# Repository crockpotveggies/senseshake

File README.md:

# Groundlark — an open source seismic acquisition platform with support for FPGAs and BISCUT AI chips

Groundlark is an open hardware seismic acquisition platform combining a
Raspberry Pi, a three-IMU DAQHAT-01 sensor HAT, a Trenz Artix-7 200T FPGA module,
and a passive geophone.

The image uses current HAT CAD and the vendor Trenz model. The Pi, baseline
socket and geophone are conceptual geometry; lead routing is illustrative.
The J1 procurement substitute needs a physical stack-height check.

## Hardware

The [DAQHAT-01](docs/trenz-hat.md) is an 85 × 56 mm, six-layer FR-4 carrier with
three XYZ LSM6DSO IMUs and one ADS122C04 input for an external Racotech geophone.
The stack is **Pi → HAT → Trenz FPGA**. It requires a separate regulated
3.3 V-class FPGA supply; follow the guide's voltage and power limits.

The [internal FPGA link](docs/fpga-host-link.md) reserves six QSPI wires and
supports UART, reset and switched Pi-driven JTAG without external ribbon cables.
Pi 4 initially uses SPI6; native quad transfers require a different host solution.
An SPI echo bitstream is implemented; accelerated sensor processing remains future work.

The [USB-C sensor head](docs/usb-sensor-head.md) carries an RM3100 magnetometer
and optional DLVR infrasound sensor. It connects to the Pi for power and data;
its MCU firmware is still pending. These sensors are separate from the HAT.
The [A2 ASIC HAT](docs/design-a0.md) and [Coldfoot integration](docs/coldfoot-integration.md)
are retained as a separate design; current hardware work focuses on the FPGA stack.

Use the [stack assembly guide](docs/stack-assembly.md) and
[JLCPCB instructions](docs/jlcpcb-assembly.md) for mechanical and manufacturing details.
The JLCPCB package targets **one assembled HAT**. Upload the corrected BOM and
CPL together. Supplier quantity, sourcing, placement and J1 fit checks remain open.
Fabrication packages stay local under ignored `hw/releases/`.

Physical power, fit, timing, noise and thermal qualification remain pending.
The [bench procedure](docs/bench-procedure.md) describes the required measurements.

## Sensor workbench

The dark-mode Python UI includes a selectable 3D HAT and geophone, six virtual
sensor streams, raw-data charts, stimulus/fault controls and recording/replay.
No hardware or Docker is required. Follow the
[beginner walkthrough](docs/sensor-workbench.md) to create your first signal.

```powershell
# Windows: set up once, then launch
./setup-ui.ps1 -Check
./ui.ps1
```

On Linux/macOS, use `sh ./setup-ui.sh --check`, then `sh ./ui.sh`.
Open **http://127.0.0.1:8080**. Tools and dependencies stay in ignored `.local/`.

This is an actual browser screenshot with simulated data. Select the geophone
can or its HAT input to highlight both and inspect the same ADC stream.
**Test HAT signals** runs eight simulated seconds through production Pi drivers
on modeled buses, with signal checks and downloadable recordings/results.
The UI simulates and replays; physical acquisition uses the [Pi software](docs/sensor-software.md).

## Project files and tests

| Directory | Contents |
| --- | --- |
| [hw/](hw/README.md) | Atopile circuits, KiCad boards, models, hardware checks and SPICE. |
| [sw/](sw/README.md) | Pi acquisition, contracts, simulator, FPGA and remote firmware interfaces. |
| [docs/](docs/README.md) | Setup, hardware specifications, assembly, interfaces and testing instructions. |
| [environment/](docs/portable-lab.md) | Pinned Docker test environment and bounded cleanup tooling. |

For the full test environment, run `./lab.ps1 build` once, then `./lab.ps1 test`.
Use `./lab.ps1 test -Profile software` for sensor contracts, acquisition,
recording/replay and recovery. See the [portable lab guide](docs/portable-lab.md)
for Linux commands, test scope, five-run retention and cleanup.

Hardware sources: [DAQHAT-01 circuit](hw/elec/hat_trenz.ato),
[KiCad PCB](hw/boards/groundlark-daqhat-01/groundlark-daqhat-01.kicad_pcb),
[A2 HAT](hw/boards/groundlark-hat/groundlark-hat.kicad_pcb), and
[USB head](hw/boards/groundlark-field-head/groundlark-field-head.kicad_pcb).
See [build instructions](docs/build.md) and [source references](docs/sources.md).

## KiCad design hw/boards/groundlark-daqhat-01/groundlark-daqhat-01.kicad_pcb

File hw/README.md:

# Hardware

| Board | Native CAD | Circuit source |
| --- | --- | --- |
| A2 Coldfoot ASIC HAT, 120 × 56 mm | [KiCad](boards/groundlark-hat/groundlark-hat.kicad_pcb) | [atopile](elec/hat.ato) |
| DAQHAT-01 Trenz FPGA HAT, 85 × 56 mm | [KiCad](boards/groundlark-daqhat-01/groundlark-daqhat-01.kicad_pcb) | [atopile](elec/hat_trenz.ato) |
| Remote USB magnetometer/infrasound head, 70 × 45 mm | [KiCad](boards/groundlark-field-head/groundlark-field-head.kicad_pcb) | [atopile](elec/field_head.ato) |

`ato.yaml` owns the build targets. `elec/` owns connectivity; `layout*.json` owns
placement metadata. `boards/` contains routed deliverables, BOMs and rendered
previews. `libraries/` and `models/` are shared dependencies with relative CAD
references. Stack concept boards are visualization artifacts, not fabrication
boards.

Use the root portable lab for routine checks. See the [build guide](../docs/build.md),
[Trenz guide](../docs/trenz-hat.md) and [validation limits](../docs/validation.md)
before invoking the lower-level authoring tools.

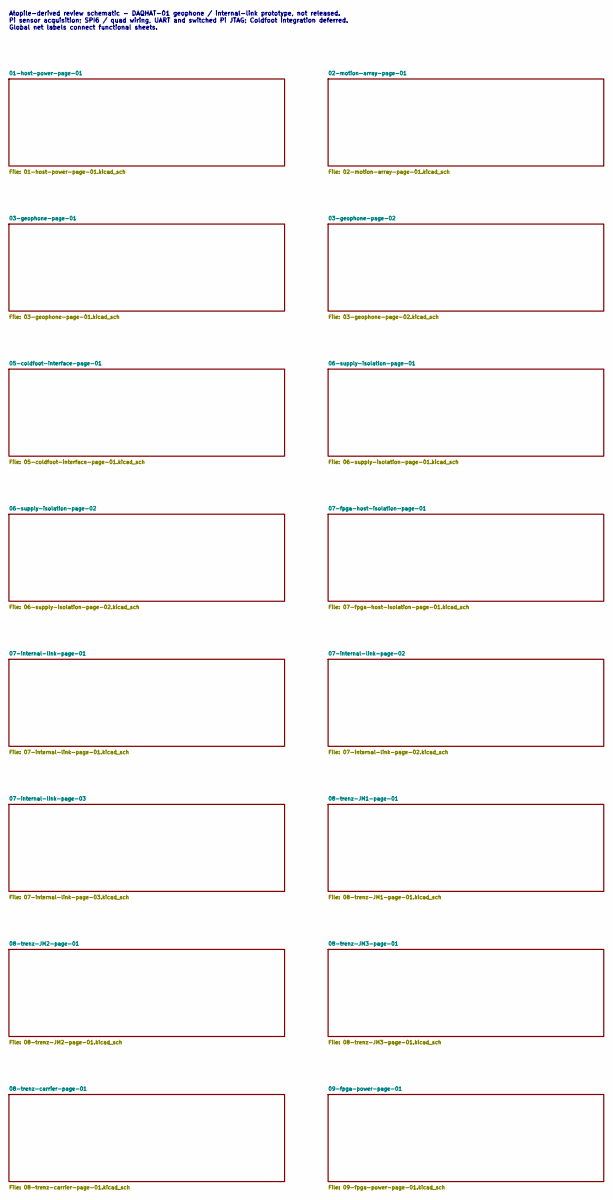
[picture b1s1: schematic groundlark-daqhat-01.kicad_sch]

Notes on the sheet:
Atopile-derived review schematic - DAQHAT-01 geophone / internal-link prototype, not released. Pi sensor acquisition; SPI6 / quad wiring, UART and switched Pi JTAG; Coldfoot integration deferred. Global net labels connect functional sheets.

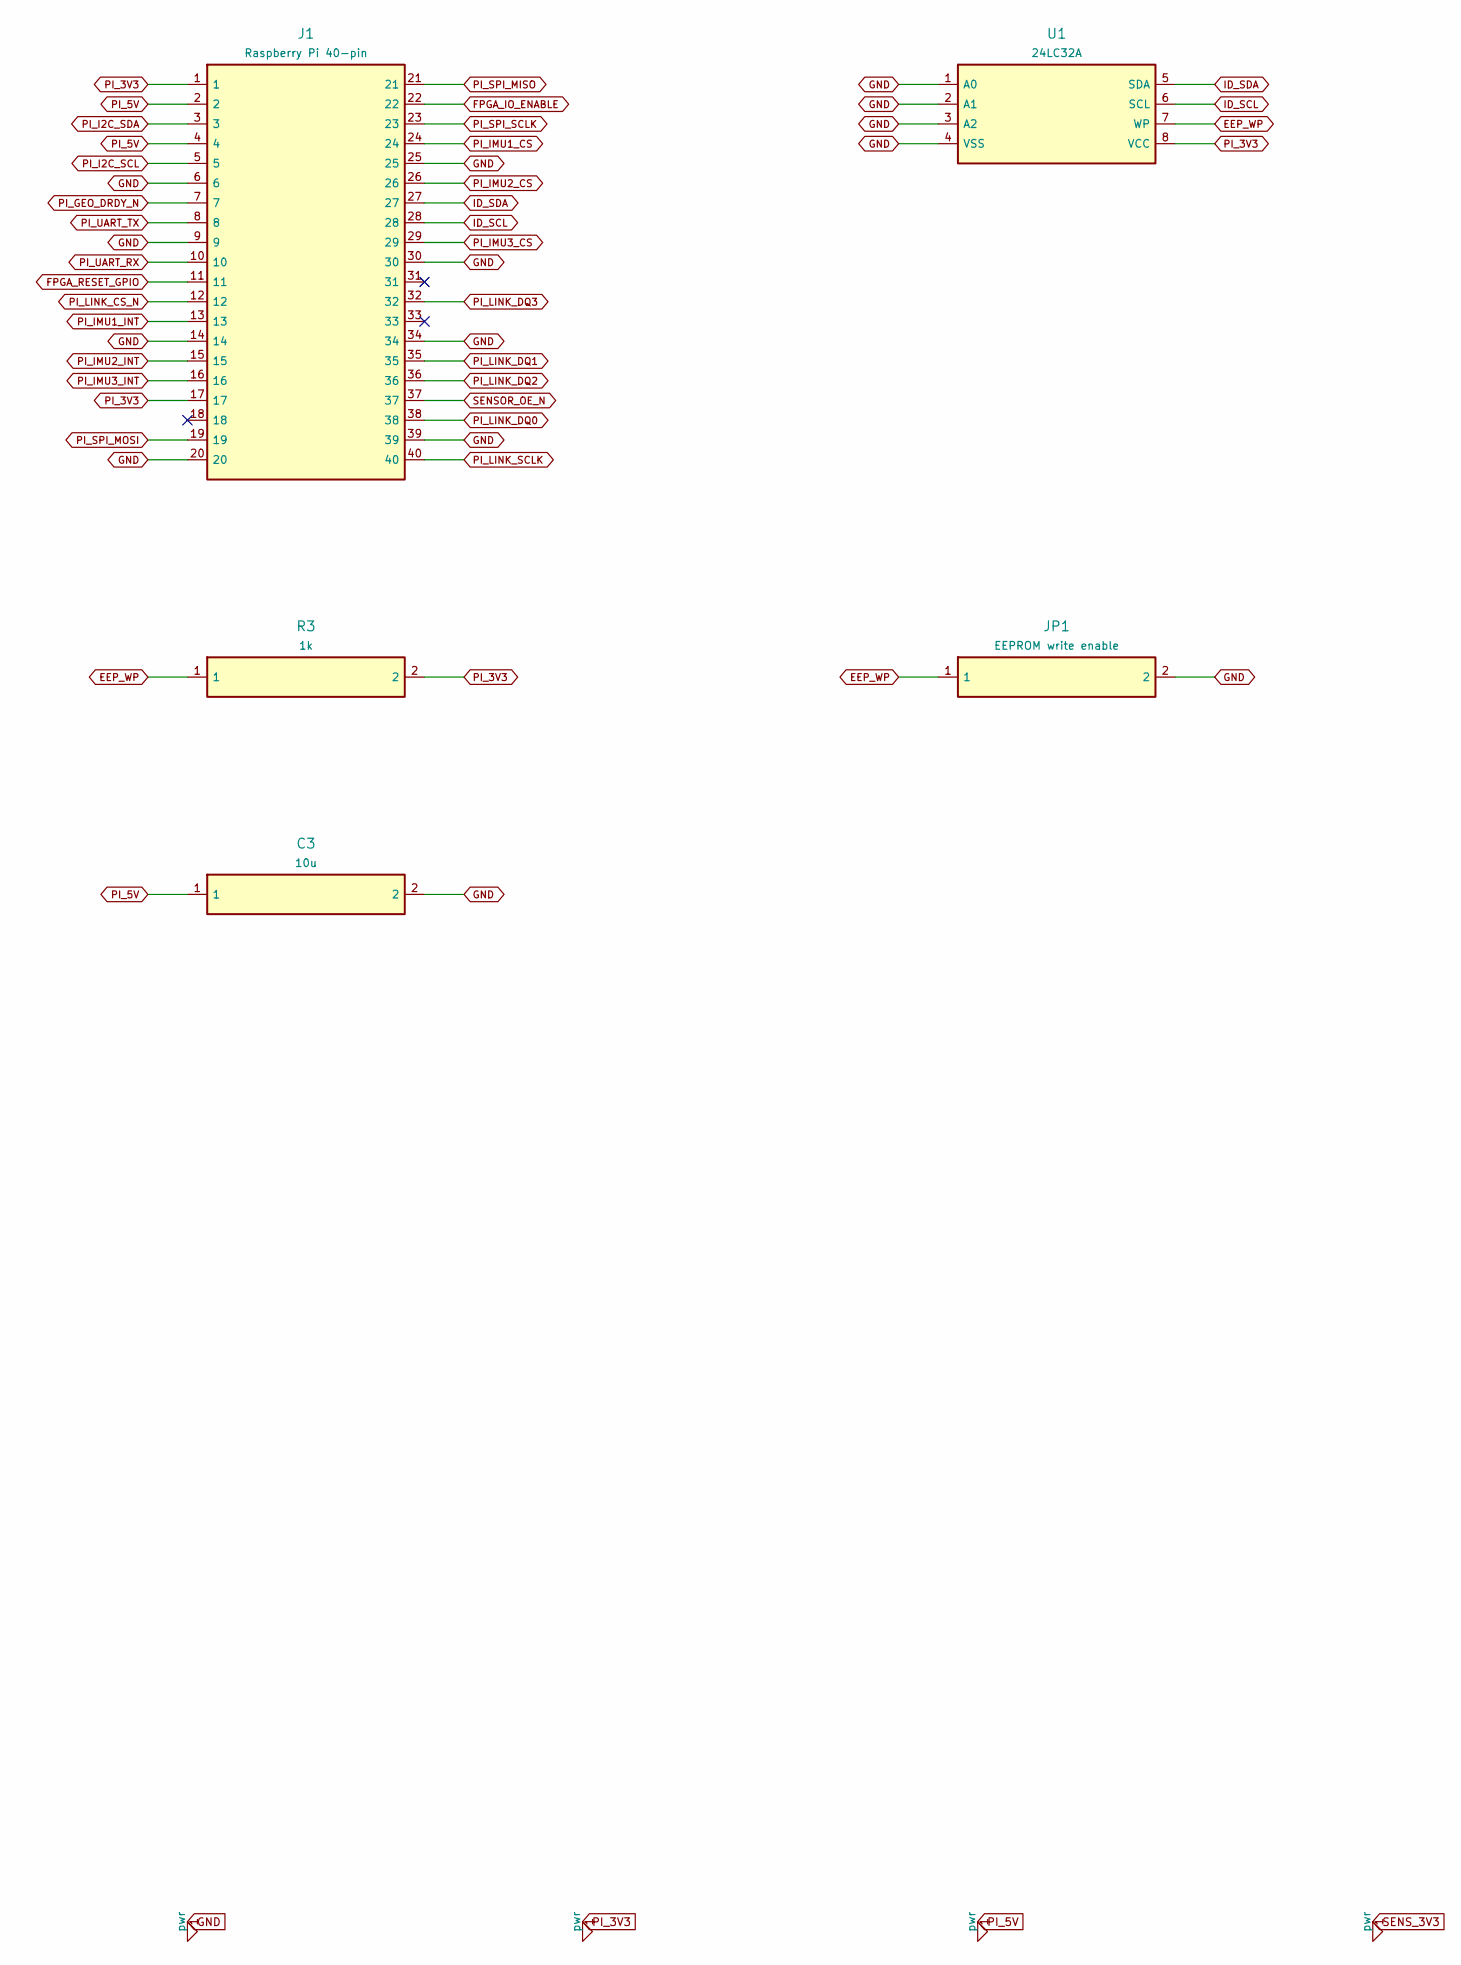
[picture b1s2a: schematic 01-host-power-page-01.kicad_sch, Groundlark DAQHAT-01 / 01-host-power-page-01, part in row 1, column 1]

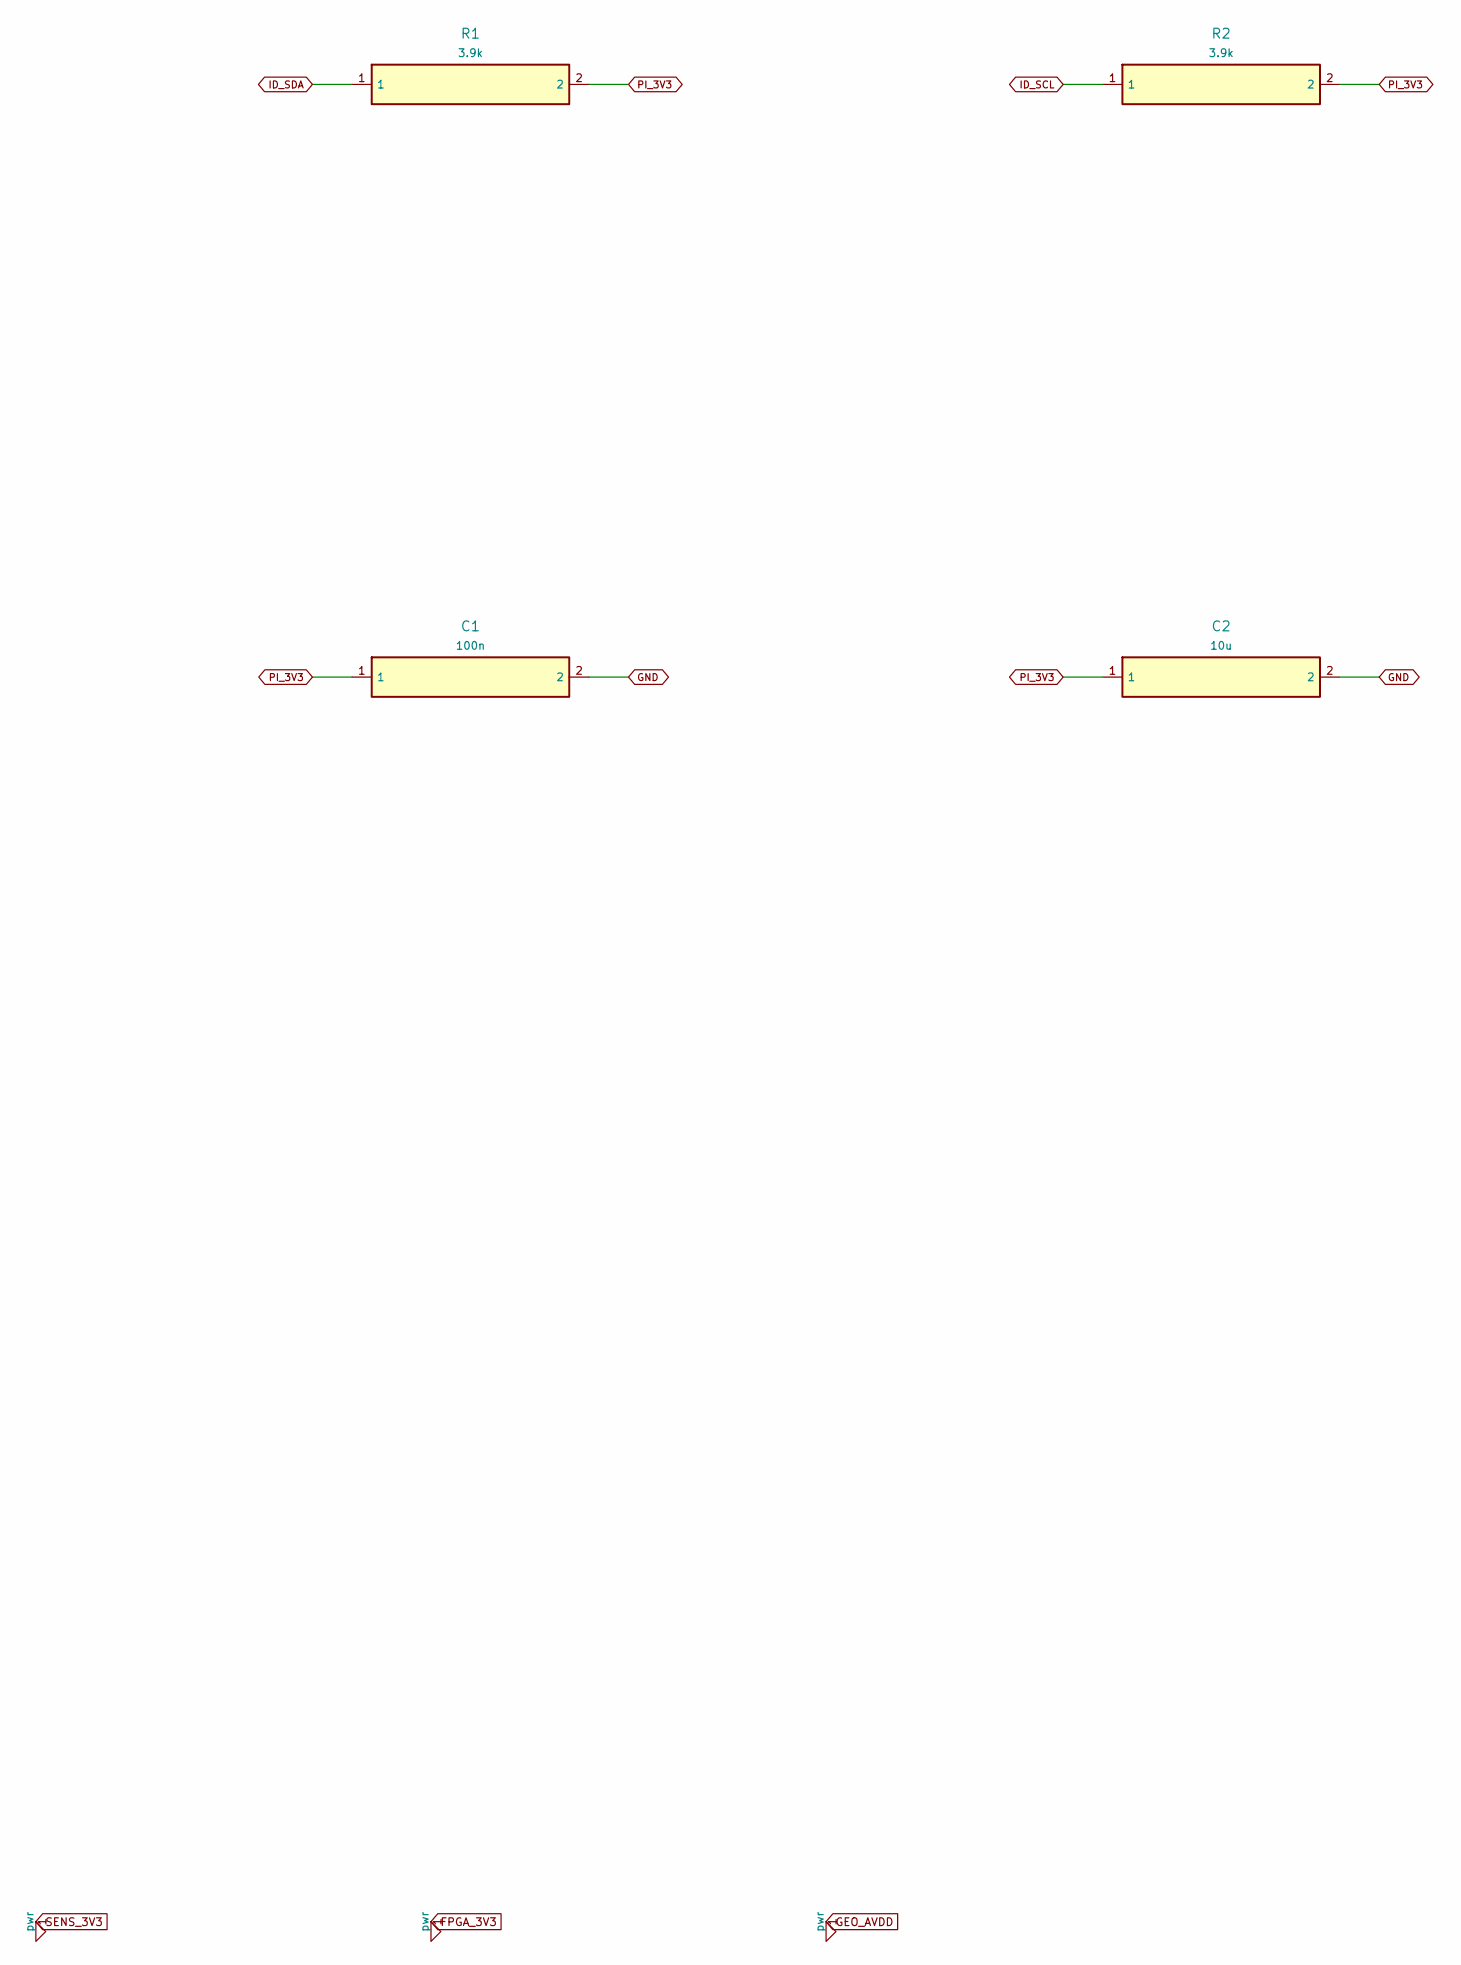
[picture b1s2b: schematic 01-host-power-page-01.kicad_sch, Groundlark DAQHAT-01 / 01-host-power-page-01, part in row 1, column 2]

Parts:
C1: 100n; Capacitor_SMD__C_0603_1608Metric; MPN GRM188R71H104KA93D
C2, C3: 10u; Capacitor_SMD__C_0805_2012Metric; MPN GRM21BR61A106KE19L
J1: Raspberry Pi 40-pin; Connector_PinHeader_2.54mm__PinHeader_2x20_P2.54mm_Vertical; MPN Samtec ESQ-120-23-G-D
JP1: EEPROM write enable; Connector_PinHeader_2.54mm__PinHeader_1x02_P2.54mm_Vertical; MPN EEPROM write enable
R1, R2: 3.9k; Resistor_SMD__R_0603_1608Metric; MPN RC0603FR-073K9L
R3: 1k; Resistor_SMD__R_0603_1608Metric; MPN RC0603FR-071KL
U1: 24LC32A; Package_SO__SOIC-8_3.9x4.9mm_P1.27mm; MPN 24LC32A-I/SN

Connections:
18: J1.18
31: J1.31
33: J1.33
EEP_WP: JP1.1, R3.1, U1.7 (WP)
FPGA_IO_ENABLE: J1.22; also elsewhere on the board
FPGA_RESET_GPIO: J1.11; also elsewhere on the board
GND: C1.2, C2.2, C3.2, J1.6, J1.9, J1.14, J1.20, J1.25, J1.30, J1.34, J1.39, JP1.2, U1.1 (A0), U1.2 (A1), U1.3 (A2), U1.4 (VSS); also elsewhere on the board
ID_SCL: J1.28, R2.1, U1.6 (SCL)
ID_SDA: J1.27, R1.1, U1.5 (SDA)
PI_3V3: C1.1, C2.1, J1.1, J1.17, R1.2, R2.2, R3.2, U1.8 (VCC); also elsewhere on the board
PI_5V: C3.1, J1.2, J1.4; also elsewhere on the board
PI_GEO_DRDY_N: J1.7; also elsewhere on the board
PI_I2C_SCL: J1.5; also elsewhere on the board
PI_I2C_SDA: J1.3; also elsewhere on the board
PI_IMU1_CS: J1.24; also elsewhere on the board
PI_IMU1_INT: J1.13; also elsewhere on the board
PI_IMU2_CS: J1.26; also elsewhere on the board
PI_IMU2_INT: J1.15; also elsewhere on the board
PI_IMU3_CS: J1.29; also elsewhere on the board
PI_IMU3_INT: J1.16; also elsewhere on the board
PI_LINK_CS_N: J1.12; also elsewhere on the board
PI_LINK_DQ0: J1.38; also elsewhere on the board
PI_LINK_DQ1: J1.35; also elsewhere on the board
PI_LINK_DQ2: J1.36; also elsewhere on the board
PI_LINK_DQ3: J1.32; also elsewhere on the board
PI_LINK_SCLK: J1.40; also elsewhere on the board
PI_SPI_MISO: J1.21; also elsewhere on the board
PI_SPI_MOSI: J1.19; also elsewhere on the board
PI_SPI_SCLK: J1.23; also elsewhere on the board
PI_UART_RX: J1.10; also elsewhere on the board
PI_UART_TX: J1.8; also elsewhere on the board
SENSOR_OE_N: J1.37; also elsewhere on the board

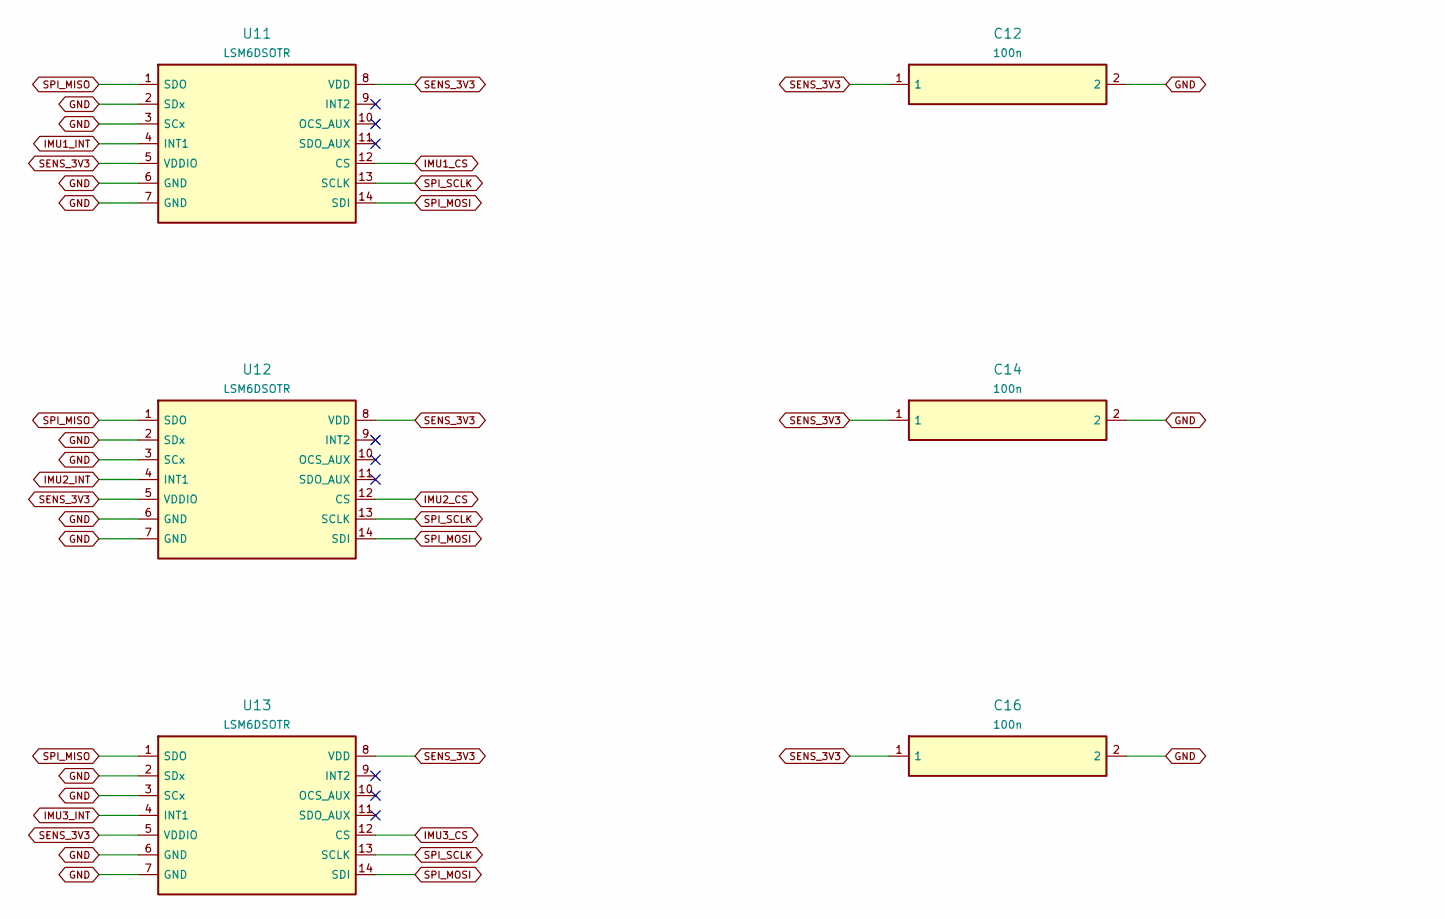
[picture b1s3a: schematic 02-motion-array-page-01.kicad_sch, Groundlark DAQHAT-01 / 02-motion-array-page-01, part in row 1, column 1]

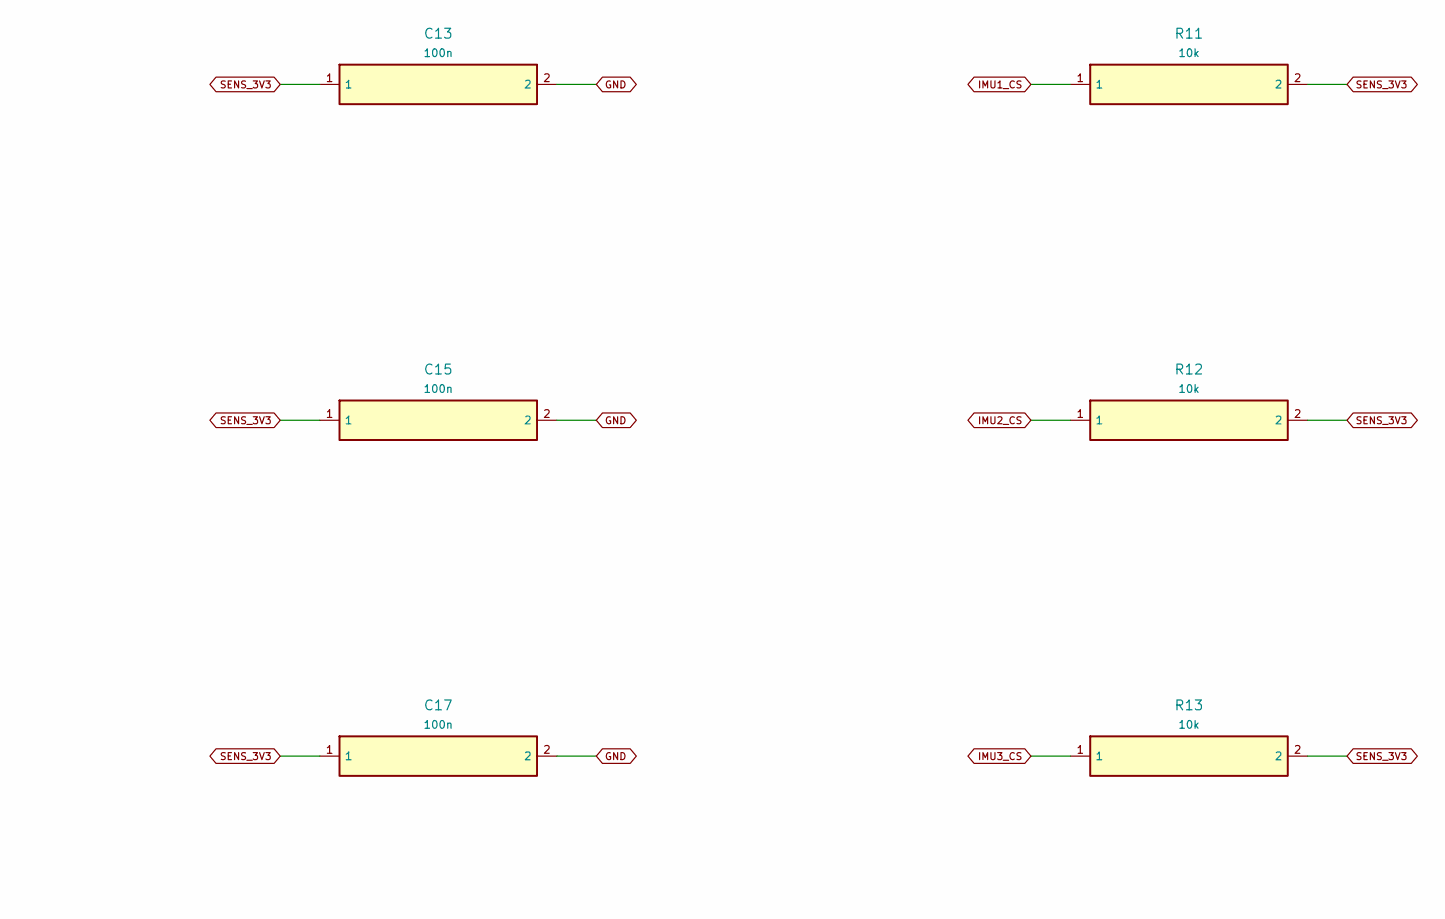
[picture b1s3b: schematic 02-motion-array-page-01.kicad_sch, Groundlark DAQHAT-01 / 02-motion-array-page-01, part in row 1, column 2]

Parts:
C12, C13, C14, C15, C16, C17: 100n; Capacitor_SMD__C_0402_1005Metric; MPN GRM155R71C104KA88D
R11, R12, R13: 10k; Resistor_SMD__R_0603_1608Metric; MPN RC0603FR-0710KL
U11, U12, U13: LSM6DSOTR; Package_LGA__LGA-14_3x2.5mm_P0.5mm_LayoutBorder3x4y; MPN LSM6DSOTR

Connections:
GND: C12.2, C13.2, C14.2, C15.2, C16.2, C17.2, U11.2 (SDx), U11.3 (SCx), U11.6 (GND), U11.7 (GND), U12.2 (SDx), U12.3 (SCx), U12.6 (GND), U12.7 (GND), U13.2 (SDx), U13.3 (SCx), U13.6 (GND), U13.7 (GND); also elsewhere on the board
IMU1_CS: R11.1, U11.12 (CS); also elsewhere on the board
IMU1_INT: U11.4 (INT1); also elsewhere on the board
IMU2_CS: R12.1, U12.12 (CS); also elsewhere on the board
IMU2_INT: U12.4 (INT1); also elsewhere on the board
IMU3_CS: R13.1, U13.12 (CS); also elsewhere on the board
IMU3_INT: U13.4 (INT1); also elsewhere on the board
SENS_3V3: C12.1, C13.1, C14.1, C15.1, C16.1, C17.1, R11.2, R12.2, R13.2, U11.5 (VDDIO), U11.8 (VDD), U12.5 (VDDIO), U12.8 (VDD), U13.5 (VDDIO), U13.8 (VDD); also elsewhere on the board
SPI_MISO: U11.1 (SDO), U12.1 (SDO), U13.1 (SDO); also elsewhere on the board
SPI_MOSI: U11.14 (SDI), U12.14 (SDI), U13.14 (SDI); also elsewhere on the board
SPI_SCLK: U11.13 (SCLK), U12.13 (SCLK), U13.13 (SCLK); also elsewhere on the board
u11-9: U11.9 (INT2)
u11-10: U11.10 (OCS_AUX)
u11-11: U11.11 (SDO_AUX)
u12-9: U12.9 (INT2)
u12-10: U12.10 (OCS_AUX)
u12-11: U12.11 (SDO_AUX)
u13-9: U13.9 (INT2)
u13-10: U13.10 (OCS_AUX)
u13-11: U13.11 (SDO_AUX)

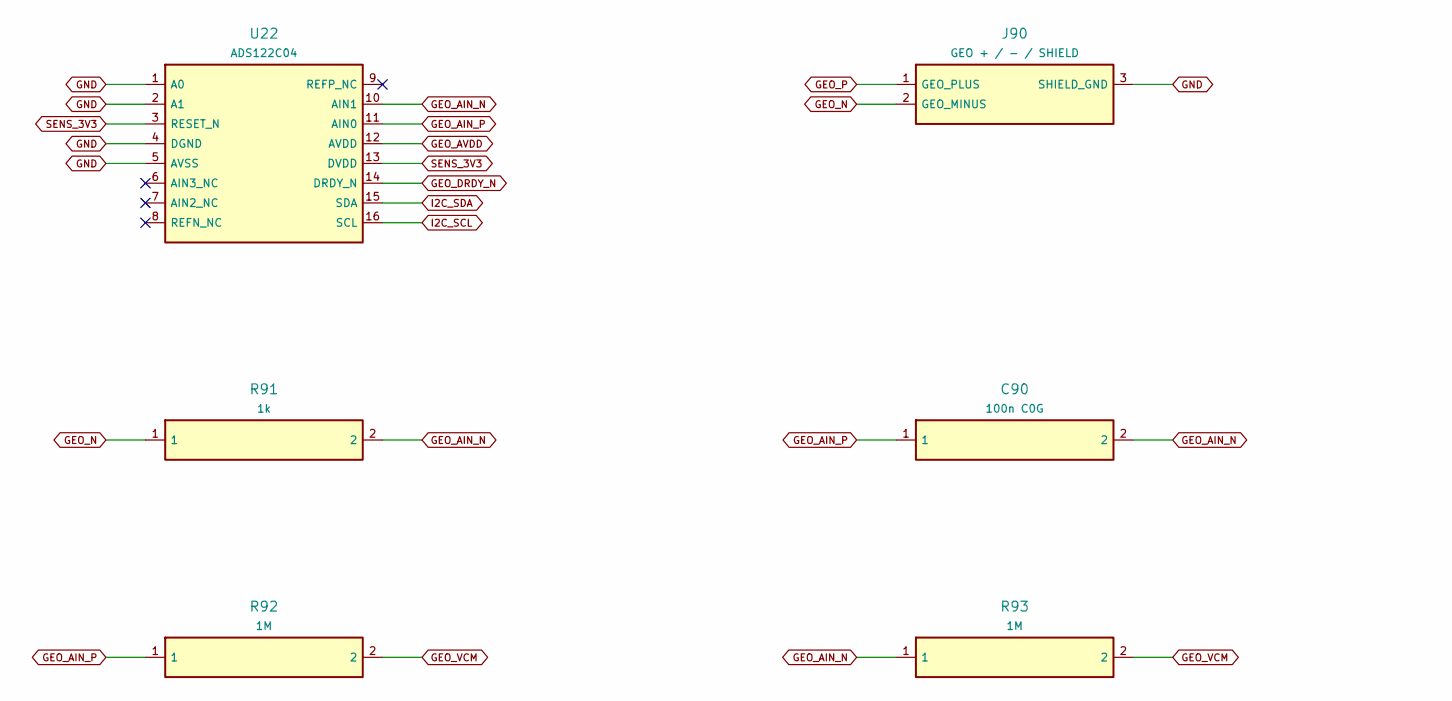
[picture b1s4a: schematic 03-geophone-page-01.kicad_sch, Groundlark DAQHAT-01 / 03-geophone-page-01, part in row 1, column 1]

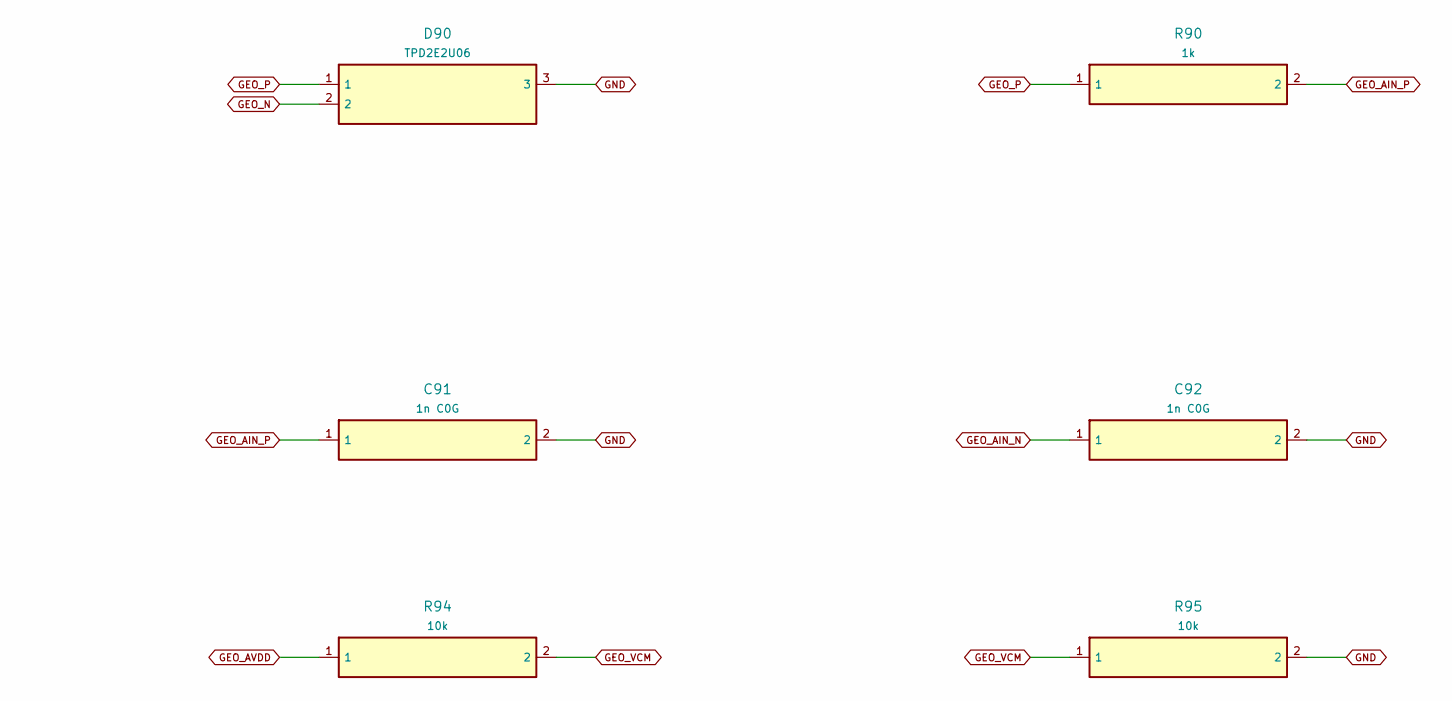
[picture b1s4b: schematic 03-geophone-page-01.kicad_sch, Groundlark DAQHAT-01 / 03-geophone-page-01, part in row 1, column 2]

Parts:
C90: 100n C0G; Capacitor_SMD__C_1206_3216Metric; MPN C3216C0G1H104J160AA
C91, C92: 1n C0G; Capacitor_SMD__C_0603_1608Metric; MPN C0603C102J5GACTU
D90: TPD2E2U06; Package_TO_SOT_SMD__SOT-323_SC-70; MPN TPD2E2U06DCKR
J90: GEO + / - / SHIELD; Connector_Phoenix_MC__PhoenixContact_MCV_1,5_3-G-3.81_1x03_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; MPN 1803439
R90, R91: 1k; Resistor_SMD__R_0603_1608Metric; MPN RC0603FR-071KL
R92, R93: 1M; Resistor_SMD__R_0603_1608Metric; MPN RC0603FR-071ML
R94, R95: 10k; Resistor_SMD__R_0603_1608Metric; MPN RC0603FR-0710KL
U22: ADS122C04; Package_SO__TSSOP-16_4.4x5mm_P0.65mm; MPN ADS122C04IPWR

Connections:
GEO_AIN_N: C90.2, C92.1, R91.2, R93.1, U22.10 (AIN1)
GEO_AIN_P: C90.1, C91.1, R90.2, R92.1, U22.11 (AIN0)
GEO_AVDD: R94.1, U22.12 (AVDD); also elsewhere on the board
GEO_DRDY_N: U22.14 (DRDY_N); also elsewhere on the board
GEO_N: D90.2, J90.2 (GEO_MINUS), R91.1
GEO_P: D90.1, J90.1 (GEO_PLUS), R90.1
GEO_VCM: R92.2, R93.2, R94.2, R95.1; also elsewhere on the board
GND: C91.2, C92.2, D90.3, J90.3 (SHIELD_GND), R95.2, U22.1 (A0), U22.2 (A1), U22.4 (DGND), U22.5 (AVSS); also elsewhere on the board
I2C_SCL: U22.16 (SCL); also elsewhere on the board
I2C_SDA: U22.15 (SDA); also elsewhere on the board
SENS_3V3: U22.3 (RESET_N), U22.13 (DVDD); also elsewhere on the board
u22-6: U22.6 (AIN3_NC)
u22-7: U22.7 (AIN2_NC)
u22-8: U22.8 (REFN_NC)
u22-9: U22.9 (REFP_NC)

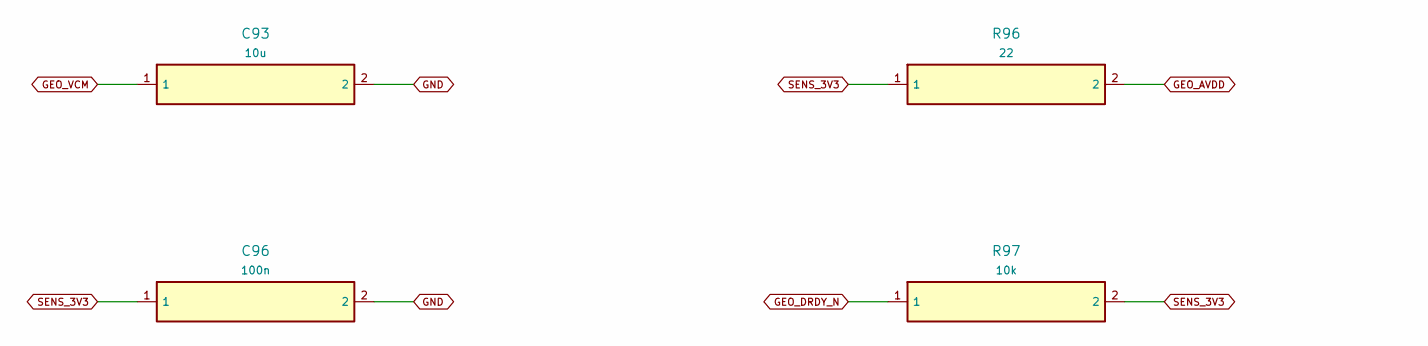
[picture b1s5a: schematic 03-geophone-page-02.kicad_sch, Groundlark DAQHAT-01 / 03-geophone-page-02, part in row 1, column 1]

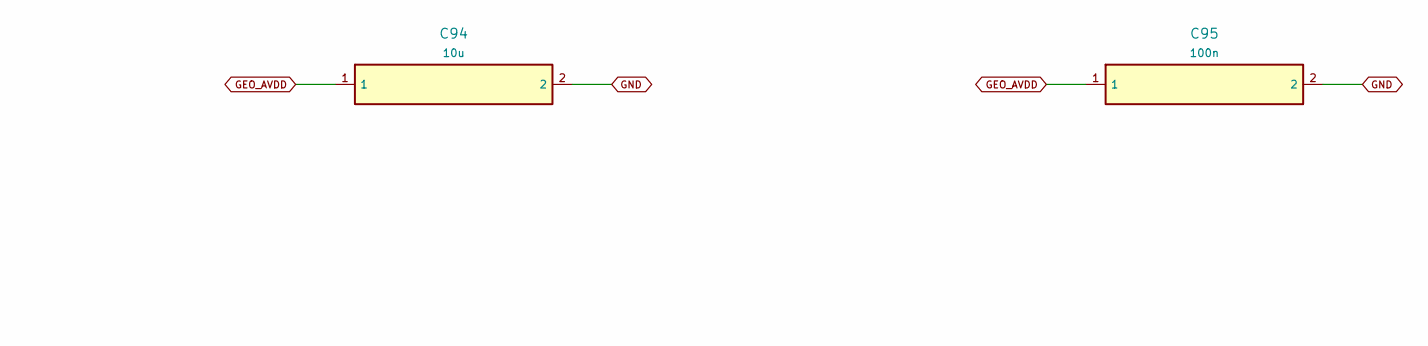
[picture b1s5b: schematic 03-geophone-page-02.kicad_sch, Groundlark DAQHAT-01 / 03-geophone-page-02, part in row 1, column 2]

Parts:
C93, C94: 10u; Capacitor_SMD__C_0805_2012Metric; MPN GRM21BR61A106KE19L
C95, C96: 100n; Capacitor_SMD__C_0603_1608Metric; MPN GRM188R71H104KA93D
R96: 22; Resistor_SMD__R_0603_1608Metric; MPN RC0603FR-0722RL
R97: 10k; Resistor_SMD__R_0603_1608Metric; MPN RC0603FR-0710KL

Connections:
GEO_AVDD: C94.1, C95.1, R96.2; also elsewhere on the board
GEO_DRDY_N: R97.1; also elsewhere on the board
GEO_VCM: C93.1; also elsewhere on the board
GND: C93.2, C94.2, C95.2, C96.2; also elsewhere on the board
SENS_3V3: C96.1, R96.1, R97.2; also elsewhere on the board

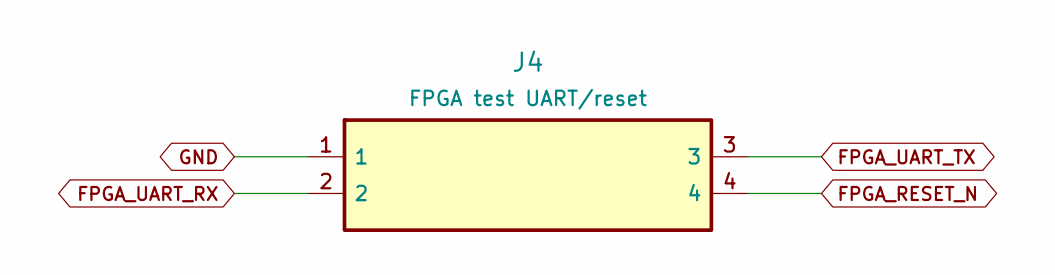
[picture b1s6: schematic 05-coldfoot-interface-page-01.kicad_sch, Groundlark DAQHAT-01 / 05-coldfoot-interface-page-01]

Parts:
J4: FPGA test UART/reset; Connector_PinHeader_2.54mm__PinHeader_1x04_P2.54mm_Vertical; MPN Coldfoot UART service ONLY

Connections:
FPGA_RESET_N: J4.4; also elsewhere on the board
FPGA_UART_RX: J4.2; also elsewhere on the board
FPGA_UART_TX: J4.3; also elsewhere on the board
GND: J4.1; also elsewhere on the board

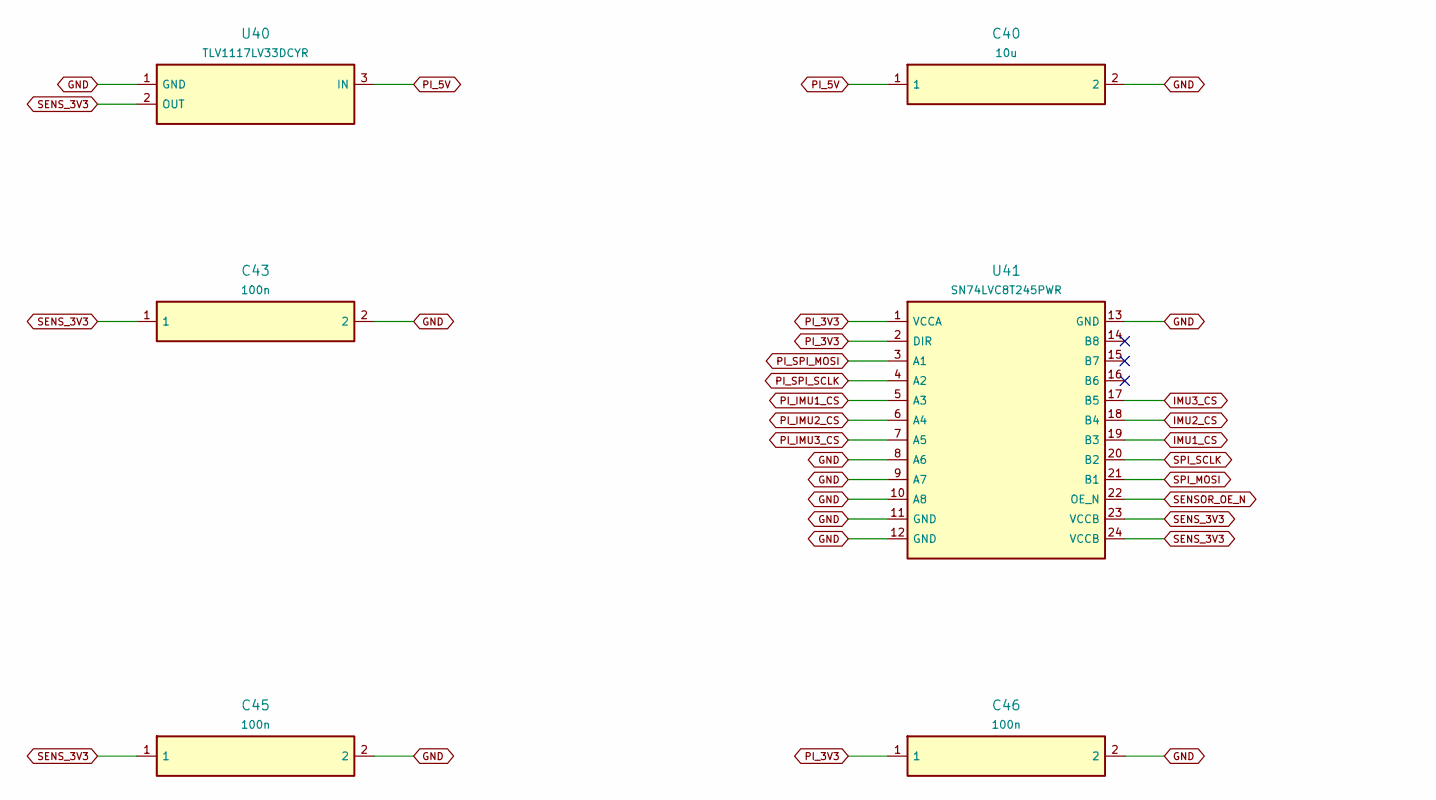
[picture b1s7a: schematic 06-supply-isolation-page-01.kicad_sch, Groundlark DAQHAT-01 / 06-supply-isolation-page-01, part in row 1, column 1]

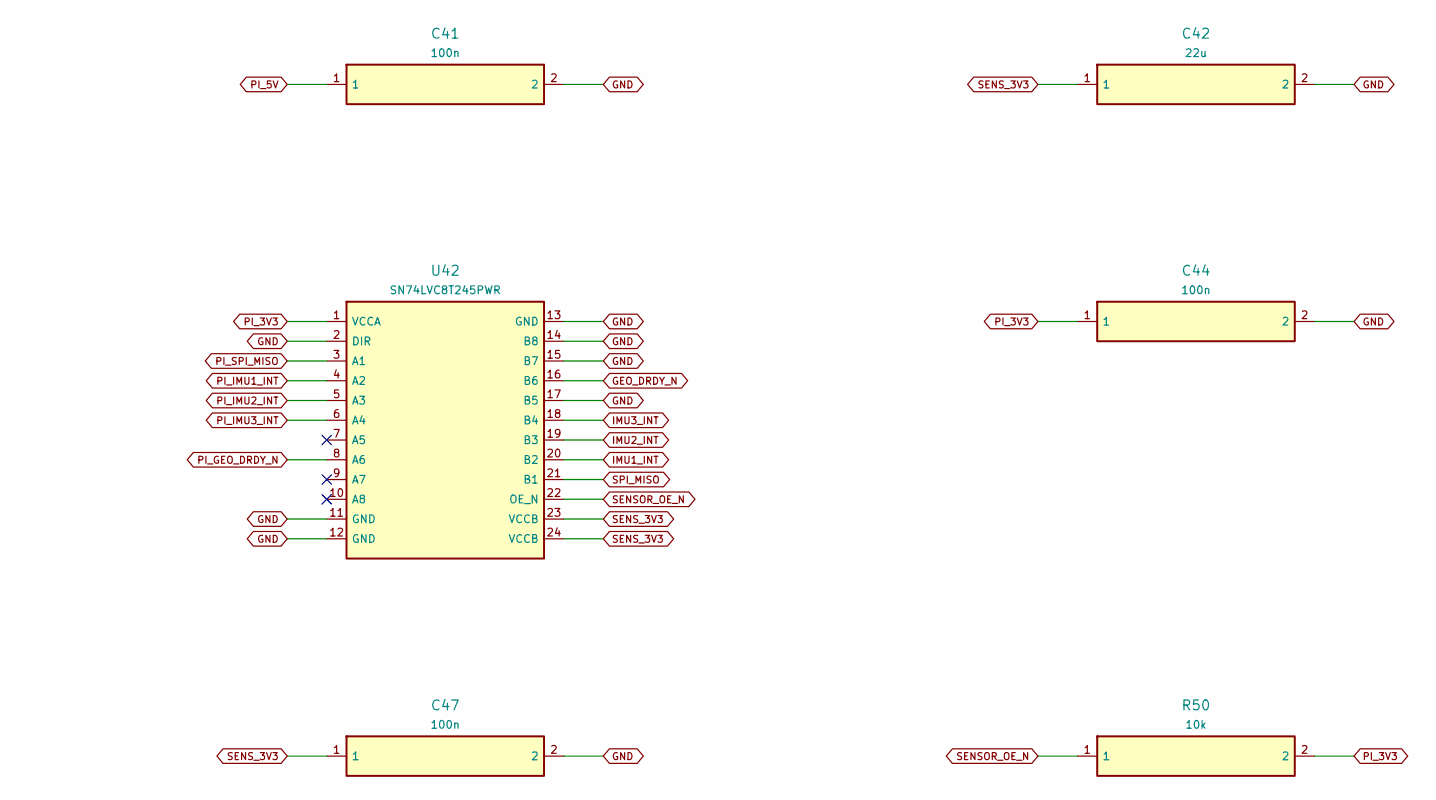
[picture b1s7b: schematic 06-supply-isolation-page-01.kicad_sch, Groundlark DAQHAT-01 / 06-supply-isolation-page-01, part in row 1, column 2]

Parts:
C40: 10u; Capacitor_SMD__C_0805_2012Metric; MPN GRM21BR61A106KE19L
C41, C43, C44, C45, C46, C47: 100n; Capacitor_SMD__C_0603_1608Metric; MPN GRM188R71H104KA93D
C42: 22u; Capacitor_SMD__C_1206_3216Metric; MPN GRM31CR61A226KE19L
R50: 10k; Resistor_SMD__R_0603_1608Metric; MPN RC0603FR-0710KL
U40: TLV1117LV33DCYR; Package_TO_SOT_SMD__SOT-223-3_TabPin2; MPN TLV1117LV33DCYR
U41, U42: SN74LVC8T245PWR; Package_SO__TSSOP-24_4.4x7.8mm_P0.65mm; MPN SN74LVC8T245PWR

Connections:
GEO_DRDY_N: U42.16 (B6); also elsewhere on the board
GND: C40.2, C41.2, C42.2, C43.2, C44.2, C45.2, C46.2, C47.2, U40.1 (GND), U41.8 (A6), U41.9 (A7), U41.10 (A8), U41.11 (GND), U41.12 (GND), U41.13 (GND), U42.2 (DIR), U42.11 (GND), U42.12 (GND), U42.13 (GND), U42.14 (B8), U42.15 (B7), U42.17 (B5); also elsewhere on the board
IMU1_CS: U41.19 (B3); also elsewhere on the board
IMU1_INT: U42.20 (B2); also elsewhere on the board
IMU2_CS: U41.18 (B4); also elsewhere on the board
IMU2_INT: U42.19 (B3); also elsewhere on the board
IMU3_CS: U41.17 (B5); also elsewhere on the board
IMU3_INT: U42.18 (B4); also elsewhere on the board
PI_3V3: C44.1, C46.1, R50.2, U41.1 (VCCA), U41.2 (DIR), U42.1 (VCCA); also elsewhere on the board
PI_5V: C40.1, C41.1, U40.3 (IN); also elsewhere on the board
PI_GEO_DRDY_N: U42.8 (A6); also elsewhere on the board
PI_IMU1_CS: U41.5 (A3); also elsewhere on the board
PI_IMU1_INT: U42.4 (A2); also elsewhere on the board
PI_IMU2_CS: U41.6 (A4); also elsewhere on the board
PI_IMU2_INT: U42.5 (A3); also elsewhere on the board
PI_IMU3_CS: U41.7 (A5); also elsewhere on the board
PI_IMU3_INT: U42.6 (A4); also elsewhere on the board
PI_SPI_MISO: U42.3 (A1); also elsewhere on the board
PI_SPI_MOSI: U41.3 (A1); also elsewhere on the board
PI_SPI_SCLK: U41.4 (A2); also elsewhere on the board
SENSOR_OE_N: R50.1, U41.22 (OE_N), U42.22 (OE_N); also elsewhere on the board
SENS_3V3: C42.1, C43.1, C45.1, C47.1, U40.2 (OUT), U41.23 (VCCB), U41.24 (VCCB), U42.23 (VCCB), U42.24 (VCCB); also elsewhere on the board
SPI_MISO: U42.21 (B1); also elsewhere on the board
SPI_MOSI: U41.21 (B1); also elsewhere on the board
SPI_SCLK: U41.20 (B2); also elsewhere on the board
u41-14: U41.14 (B8)
u41-15: U41.15 (B7)
u41-16: U41.16 (B6)
u42-7: U42.7 (A5)
u42-9: U42.9 (A7)
u42-10: U42.10 (A8)
